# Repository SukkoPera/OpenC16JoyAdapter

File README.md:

# OpenC16JoyAdapter
OpenC16JoyAdapter is an Open Hardware Joystick Adapter for C-16, Plus/4 and the rest of the Commodore 264 family.

### Summary
Based on [work by Levente Hársfalvi](http://www.zimmers.net/anonftp/pub/cbm/documents/projects/interfaces/plus4joy/plus4joy.html).

### Installation
TBD

### Configuration
TBD

### License
OpenC16JoyAdapter is Open Hardware. If you make any modifications to the board, please contribute them back.

### Support the Project
Since the project is open you are free to get the PCBs made by your preferred manufacturer, however in case you want to support the development, you can order them from PCBWay through this link:

You get cheap, professionally-made and good quality PCBs, I get some credit that will help with this and [other projects](https://www.pcbway.com/project/member/shareproject/?bmbid=41100). You won't even have to worry about the various PCB options, it's all pre-configured for you!

Also, if you still have to register to that site, [you can use this link](https://www.pcbway.com/setinvite.aspx?inviteid=41100) to get some bonus initial credit (and yield me some more).

Again, if you want to use another manufacturer, feel free to, don't feel obligated :).

### Get Support
If you need help or have questions, you can join [the official Telegram group](https://t.me/joinchat/HUHdWBC9J9JnYIrvTYfZmg).

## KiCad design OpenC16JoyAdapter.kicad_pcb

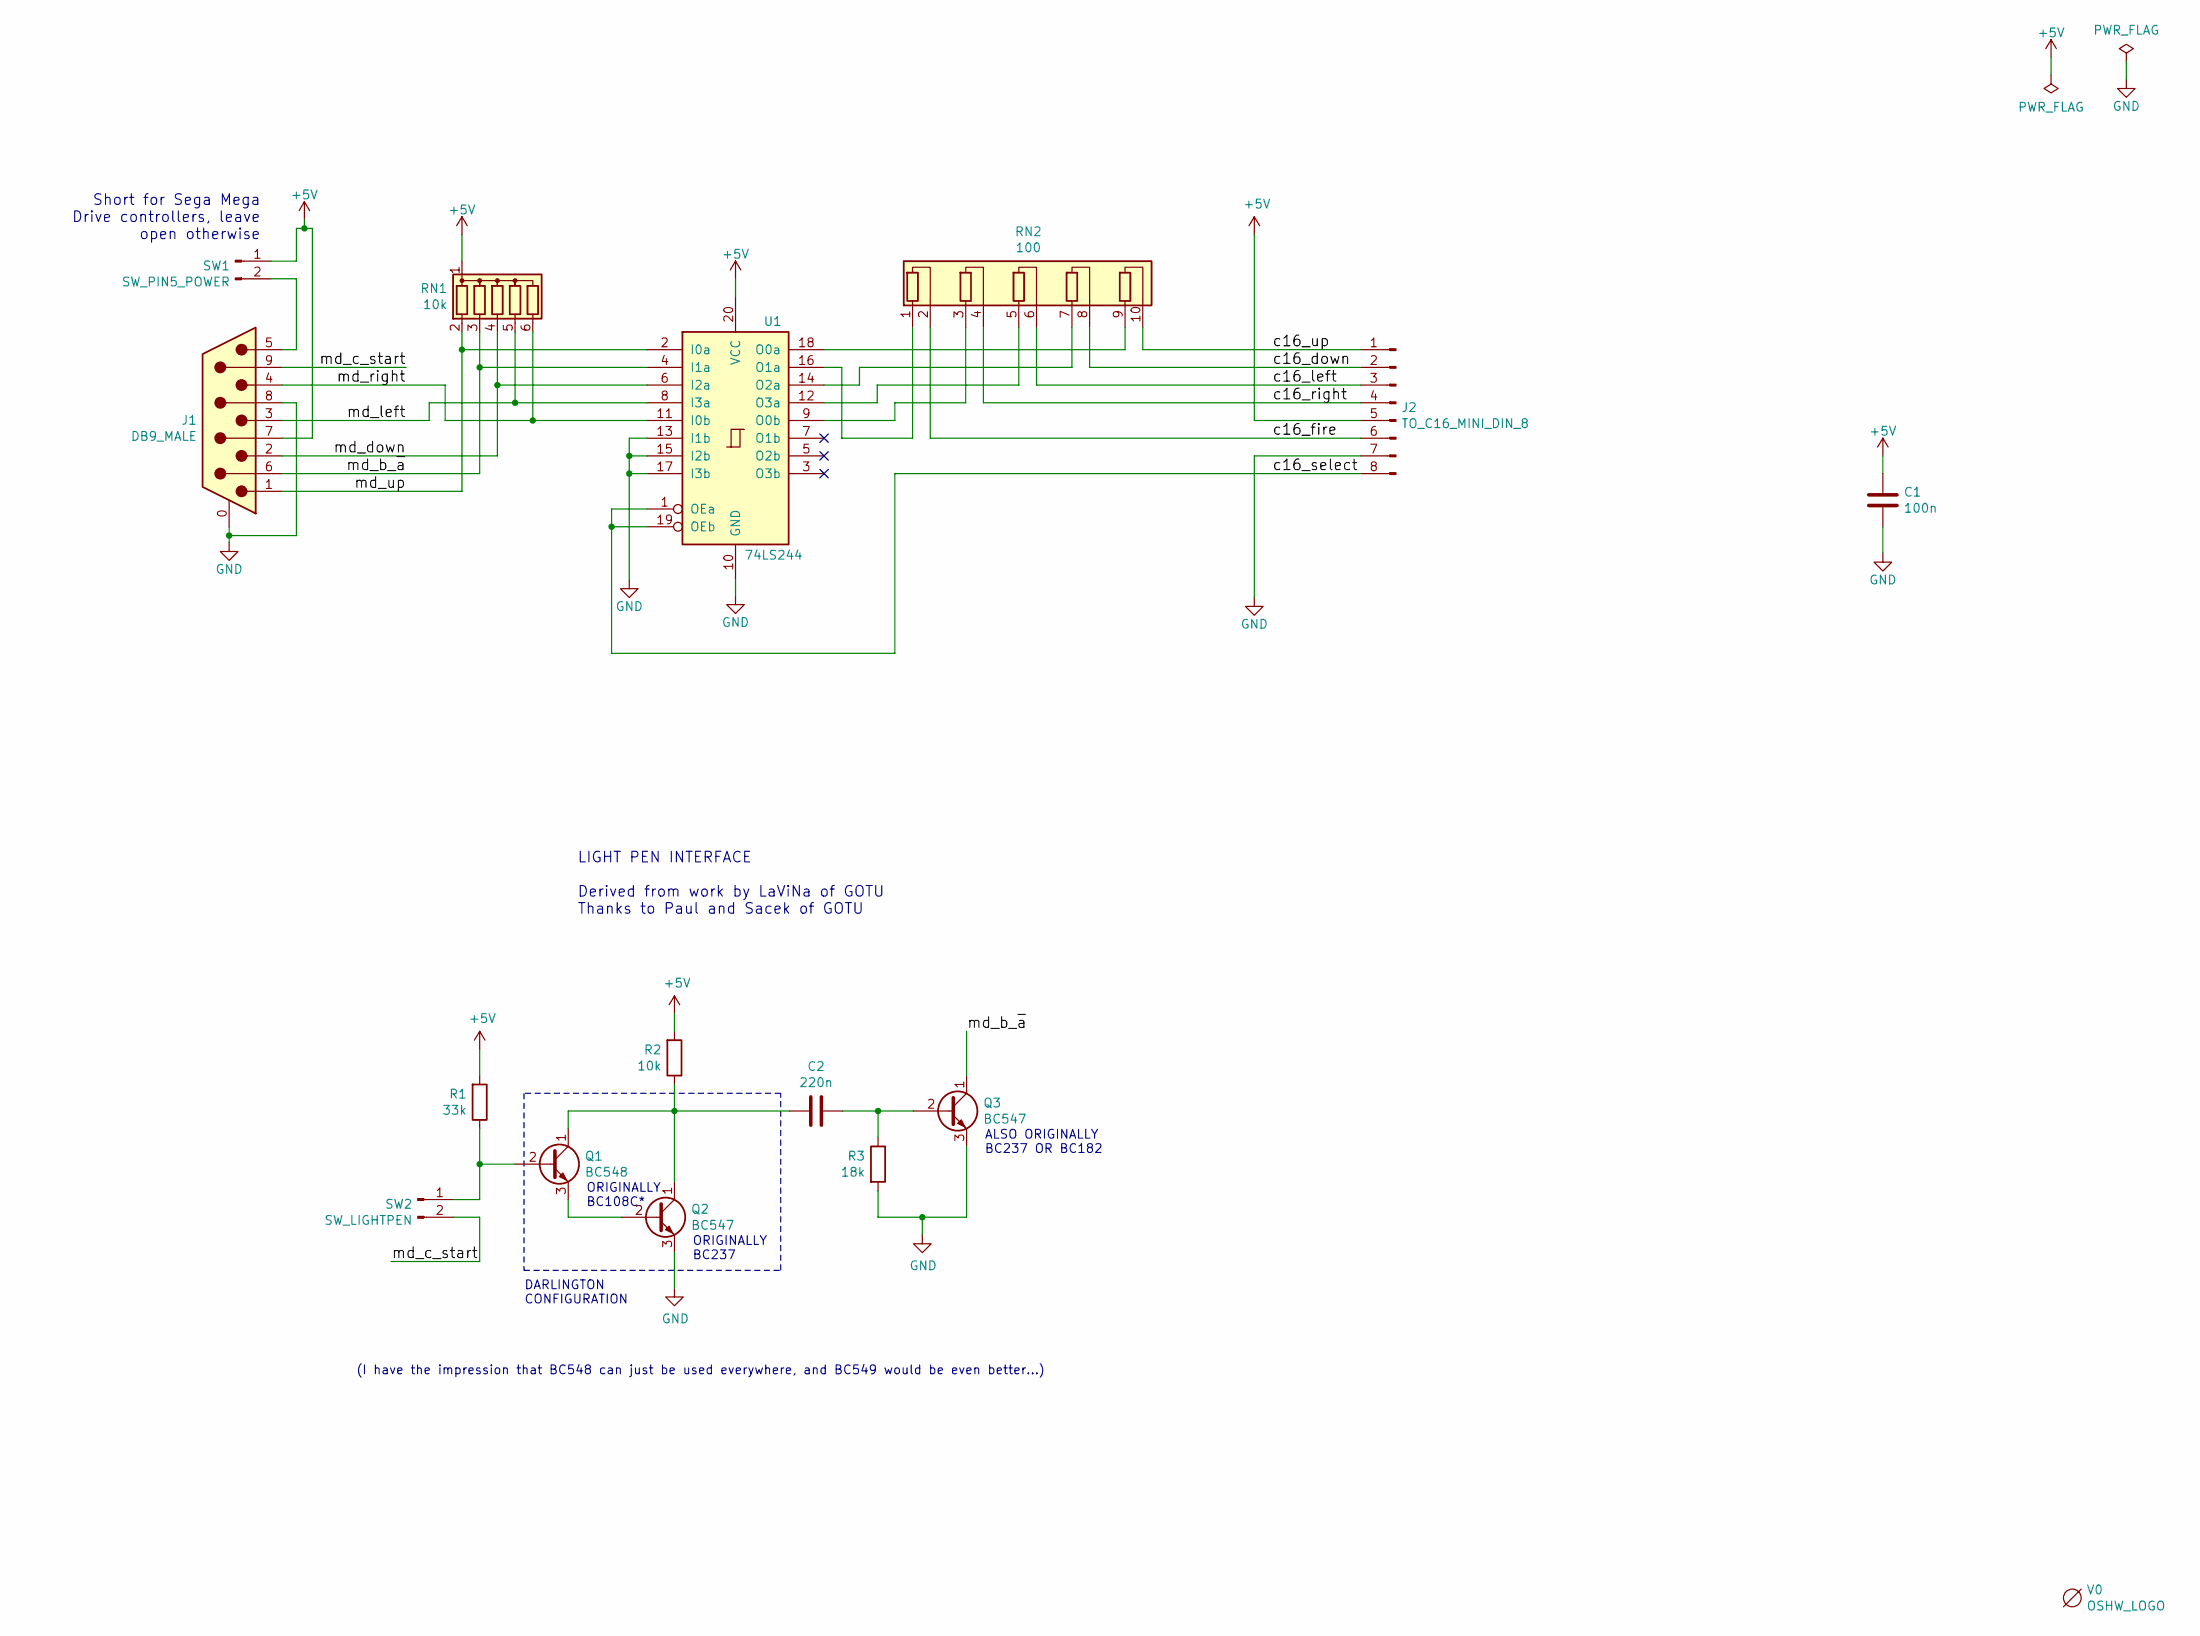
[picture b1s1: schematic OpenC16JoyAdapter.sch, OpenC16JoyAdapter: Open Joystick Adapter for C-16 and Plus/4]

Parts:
C1: 100n; C_Disc_D7.0mm_W2.5mm_P5.00mm
C2: 220n; C_Disc_D7.0mm_W2.5mm_P5.00mm
J1: DB9_MALE; DB_9M
J2: TO_C16_MINI_DIN_8; PinHeader_1x08_P2.54mm_Vertical
Q1: BC548; TO-92_HandSolder
Q2, Q3: BC547; TO-92_HandSolder
R1: 33k; R_Axial_DIN0207_L6.3mm_D2.5mm_P2.54mm_Vertical
R2: 10k; R_Axial_DIN0207_L6.3mm_D2.5mm_P2.54mm_Vertical
R3: 18k; R_Axial_DIN0207_L6.3mm_D2.5mm_P2.54mm_Vertical
RN1: 10k; R_Array_SIP6
RN2: 100; R_Array_SIP10
SW1: SW_PIN5_POWER; PinHeader_1x02_P2.54mm_Vertical
SW2: SW_LIGHTPEN; PinHeader_1x02_P2.54mm_Vertical
U1: 74LS244; DIP-20_W7.62mm_Socket_LongPads
V0: OSHW_LOGO; OSHW-Logo_5.7x6mm_Copper

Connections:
+5V: C1.1, J1.7, J2.5, R1.2, R2.2, RN1.1 (common), SW1.1, U1.20 (VCC)
/c16_down: J2.2, RN2.8 (R4.2)
/c16_fire: J2.6, RN2.2 (R1.2)
/c16_left: J2.3, RN2.6 (R3.2)
/c16_right: J2.4, RN2.4 (R2.2)
/c16_select: J2.8, U1.1 (OEa), U1.19 (OEb)
/c16_up: J2.1, RN2.10 (R5.2)
/md_b_~a: J1.6, Q3.1 (C), RN1.3 (R2), U1.4 (I1a)
/md_c_start: J1.9, SW2.2
/md_down: J1.2, RN1.4 (R3), U1.6 (I2a)
/md_left: J1.3, RN1.5 (R4), U1.8 (I3a)
/md_right: J1.4, RN1.6 (R5), U1.11 (I0b)
/md_up: J1.1, RN1.2 (R1), U1.2 (I0a)
GND: C1.2, J1.0 (PAD), J1.8, J2.7, Q2.3 (E), Q3.3 (E), R3.2, U1.10 (GND), U1.13 (I1b), U1.15 (I2b), U1.17 (I3b)
unnamed: C2.1, Q3.2 (B), R3.1
unnamed: C2.2, Q1.1 (C), Q2.1 (C), R2.1
unnamed: J1.5, SW1.2
unnamed: Q1.2 (B), R1.1, SW2.1
unnamed: Q1.3 (E), Q2.2 (B)
unnamed: RN2.1 (R1.1), U1.16 (O1a)
unnamed: RN2.3 (R2.1), U1.9 (O0b)
unnamed: RN2.5 (R3.1), U1.12 (O3a)
unnamed: RN2.7 (R4.1), U1.14 (O2a)
unnamed: RN2.9 (R5.1), U1.18 (O0a)

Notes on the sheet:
Short for Sega Mega Drive controllers, leave open otherwise
ALSO ORIGINALLY BC237 OR BC182
DARLINGTON CONFIGURATION
ORIGINALLY BC108C*
ORIGINALLY BC237
(I have the impression that BC548 can just be used everywhere, and BC549 would be even better...)
LIGHT PEN INTERFACE Derived from work by LaViNa of GOTU Thanks to Paul and Sacek of GOTU

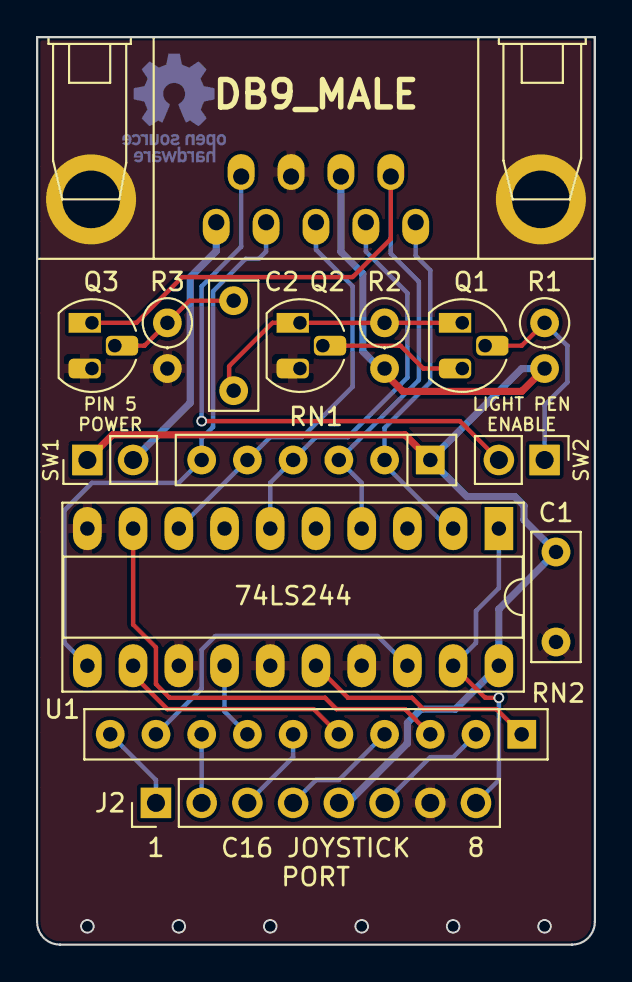
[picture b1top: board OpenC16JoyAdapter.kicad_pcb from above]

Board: 2 copper layers, 31.0 x 50.4 mm, 16 parts (1 on the bottom side), 24 nets.

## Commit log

2017-09-26 Fix bad labels and other minor modifications
2017-09-26 Use HandSoldering footprints for 0805 components
2017-09-26 Refined board a bit
2017-09-27 Smooth lower corners, stitch ground planes, fix 3D models, add version no.
2017-09-27 Make power tracks wider, fix bottom ground plane
2017-12-31 All-THT version, add pull-ups, remove led
2018-01-01 Minor tweaks
2018-01-01 Make pull-up a normal jumper and add silkscreen
2018-01-01 Make power track wider
2018-01-01 Add renders
2018-01-01 Use my README template
2018-01-05 Final touches for V2
2024-01-27 Add MiniDIN-8 pin mapping
2024-01-27 Port to KiCad 5, remove pull-up jumper, tidy up, improve routing
2024-01-27 Minor changes
2024-09-13 Integrate light pen circuit
2024-09-14 Add light pen circuit to PCB
2024-09-14 Final touches

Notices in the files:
OpenC16JoyAdapter.kicad_pcb:
Licensed under CERN OHL v.1.2
CERN OHL v.1.2
